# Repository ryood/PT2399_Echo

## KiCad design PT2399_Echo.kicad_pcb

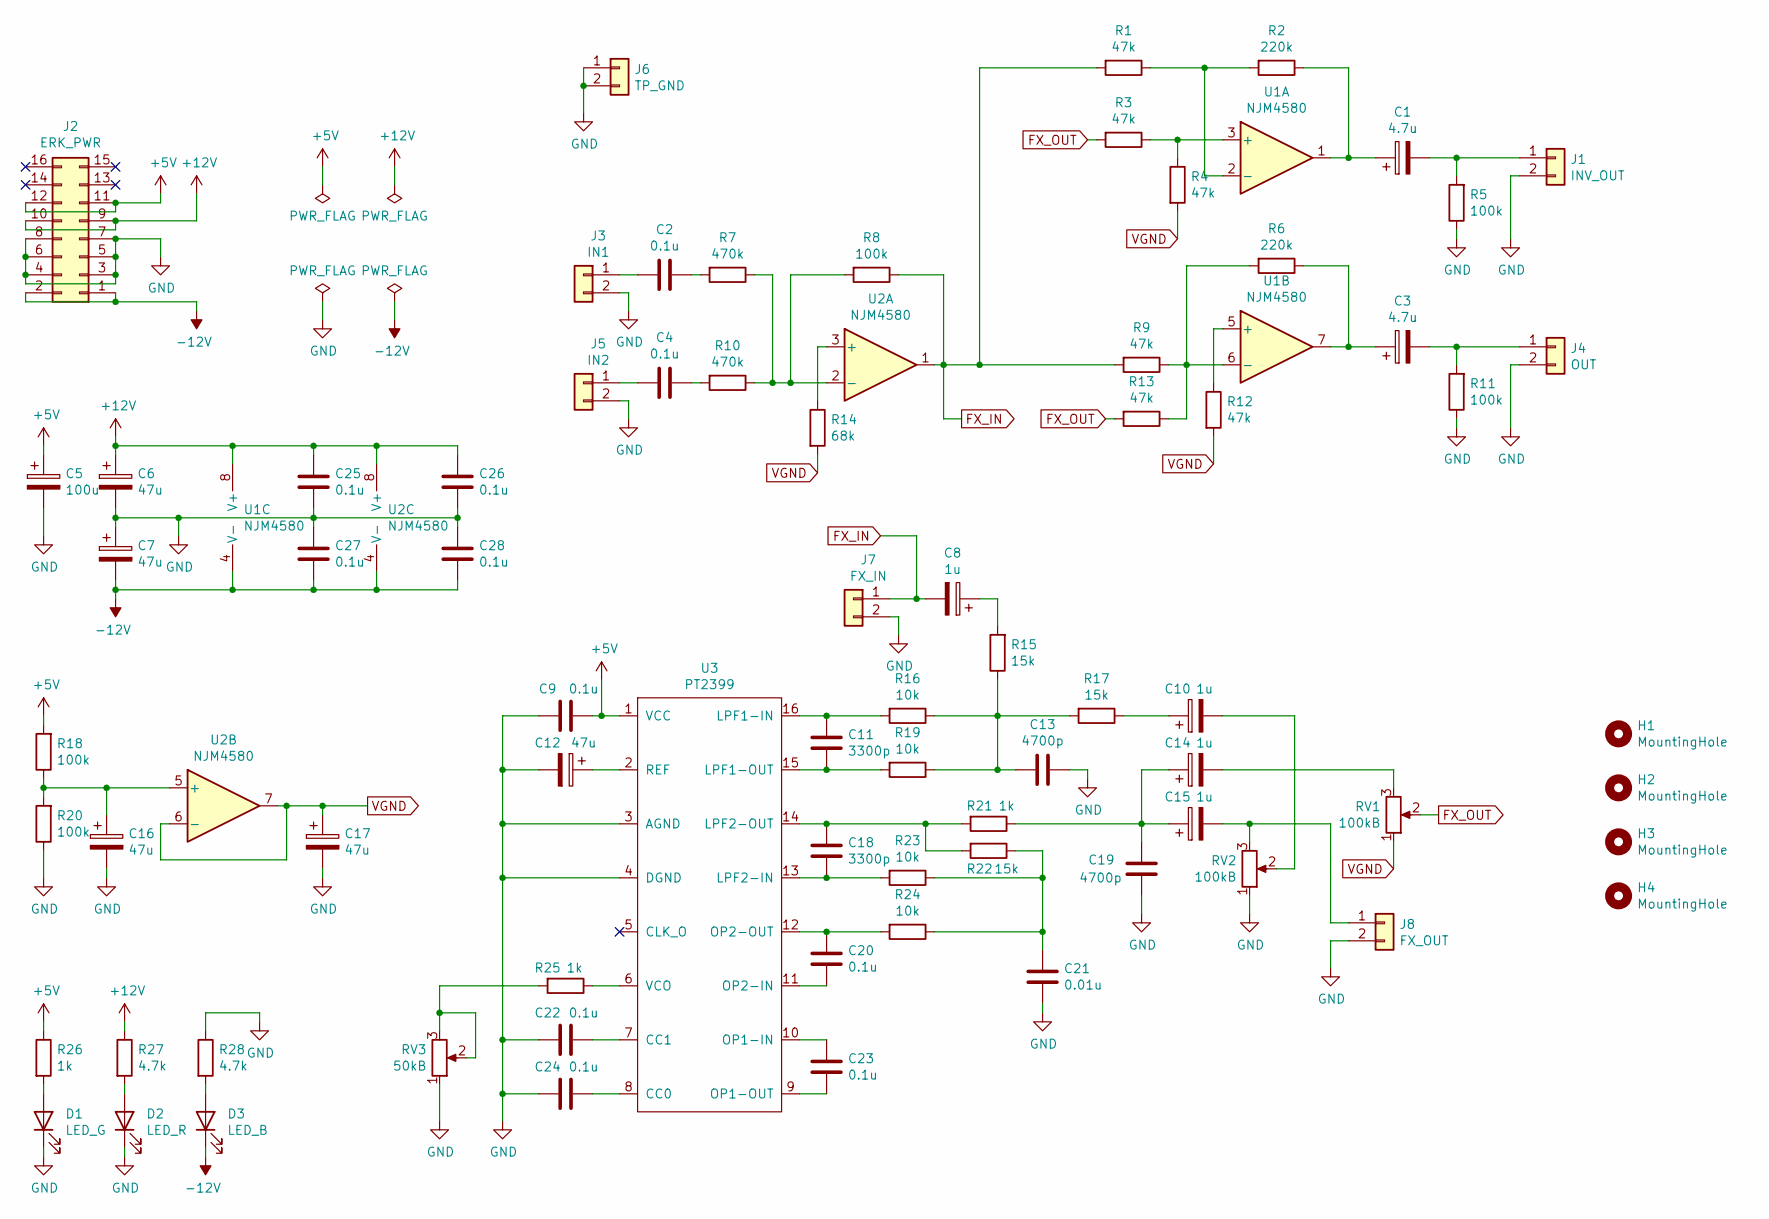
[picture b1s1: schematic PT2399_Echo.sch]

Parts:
C1, C3: 4.7u; CP_Radial_D6.3mm_P2.50mm
C2, C4, C20, C23: 0.1u; C_Rect_L7.2mm_W3.5mm_P5.00mm_FKS2_FKP2_MKS2_MKP2
C5: 100u; CP_Radial_D6.3mm_P2.50mm
C6, C7, C12, C16, C17: 47u; CP_Radial_D6.3mm_P2.50mm
C8, C10, C14, C15: 1u; CP_Radial_D6.3mm_P2.50mm
C9: 0.1u; C_Disc_D4.3mm_W1.9mm_P5.00mm
C11, C18: 3300p; C_Rect_L7.0mm_W3.5mm_P5.00mm
C13, C19: 4700p; C_Rect_L7.0mm_W3.5mm_P5.00mm
C21: 0.01u; C_Rect_L7.2mm_W3.5mm_P5.00mm_FKS2_FKP2_MKS2_MKP2
C22, C24, C25, C26, C27, C28: 0.1u; C_Disc_D3.0mm_W1.6mm_P2.50mm
D1: LED_G; LED_D3.0mm
D2: LED_R; LED_D3.0mm
D3: LED_B; LED_D3.0mm
H1, H2, H3, H4: MountingHole; MountingHole_3.2mm_M3
J1: INV_OUT; JST_XH_B2B-XH-A_1x02_P2.50mm_Vertical
J2: ERK_PWR; IDC-Header_2x08_P2.54mm_Vertical
J3: IN1; JST_XH_B2B-XH-A_1x02_P2.50mm_Vertical
J4: OUT; JST_XH_B2B-XH-A_1x02_P2.50mm_Vertical
J5: IN2; JST_XH_B2B-XH-A_1x02_P2.50mm_Vertical
J6: TP_GND; PinHeader_1x02_P2.54mm_Vertical
J7: FX_IN; JST_XH_B2B-XH-A_1x02_P2.50mm_Vertical
J8: FX_OUT; JST_XH_B2B-XH-A_1x02_P2.50mm_Vertical
R1, R3, R4, R9, R12, R13: 47k; R_Axial_DIN0207_L6.3mm_D2.5mm_P10.16mm_Horizontal
R2, R6: 220k; R_Axial_DIN0207_L6.3mm_D2.5mm_P10.16mm_Horizontal
R5, R8, R11, R18, R20: 100k; R_Axial_DIN0207_L6.3mm_D2.5mm_P10.16mm_Horizontal
R7, R10: 470k; R_Axial_DIN0207_L6.3mm_D2.5mm_P10.16mm_Horizontal
R14: 68k; R_Axial_DIN0207_L6.3mm_D2.5mm_P10.16mm_Horizontal
R15, R17, R22: 15k; R_Axial_DIN0207_L6.3mm_D2.5mm_P10.16mm_Horizontal
R16, R19, R23, R24: 10k; R_Axial_DIN0207_L6.3mm_D2.5mm_P10.16mm_Horizontal
R21, R25, R26: 1k; R_Axial_DIN0207_L6.3mm_D2.5mm_P10.16mm_Horizontal
R27, R28: 4.7k; R_Axial_DIN0207_L6.3mm_D2.5mm_P10.16mm_Horizontal
RV1, RV2: 100kB; Potentiometer_Alps_RK097_Single_Horizontal
RV3: 50kB; Potentiometer_Alps_RK097_Single_Horizontal
U1, U2: NJM4580; DIP-8_W7.62mm_Socket_LongPads
U3: PT2399; DIP-16_W7.62mm_Socket_LongPads

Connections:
+5V: C5.1, C9.1, J2.11, J2.12, R18.2, R26.1, U3.1 (VCC)
+12V: C6.1, C25.1, C26.1, J2.9, J2.10, R27.1, U1.8 (V+), U2.8 (V+)
-12V: C7.2, C27.2, C28.2, D3.1 (K), J2.1, J2.2, U1.4 (V-), U2.4 (V-)
FX_IN: C8.2, J7.1, R1.2, R8.1, R9.2, U2.1
FX_OUT: R3.2, R13.2, RV1.2
GND: C5.2, C6.2, C7.1, C9.2, C12.2, C13.1, C16.2, C17.2, C19.2, C21.2, C22.2, C24.2, C25.2, C26.2, C27.1, C28.1, D1.1 (K), D2.1 (K), J1.2, J2.3, J2.4, J2.5, J2.6, J2.7, J2.8, J3.2, J4.2, J5.2, J6.1, J6.2, J7.2, J8.2, R5.1, R11.1, R20.1, R28.1, RV2.1, RV3.1, U3.3 (AGND), U3.4 (DGND)
unnamed: C1.1, R2.1, U1.1
unnamed: C1.2, J1.1, R5.2
unnamed: C2.1, R7.2
unnamed: C2.2, J3.1
unnamed: C3.1, R6.1, U1.7
unnamed: C3.2, J4.1, R11.2
unnamed: C4.1, R10.2
unnamed: C4.2, J5.1
unnamed: C8.1, R15.2
unnamed: C10.1, R17.1
unnamed: C10.2, RV2.2
unnamed: C11.1, R16.2, U3.16 (LPF1-IN)
unnamed: C11.2, R19.2, U3.15 (LPF1-OUT)
unnamed: C12.1, U3.2 (REF)
unnamed: C13.2, R15.1, R16.1, R17.2, R19.1
unnamed: C14.1, C15.1, C19.1, R21.1
unnamed: C14.2, RV1.3
unnamed: C15.2, J8.1, RV2.3
unnamed: C16.1, R18.1, R20.2, U2.5 (+)
unnamed: C18.1, R21.2, R22.2, U3.14 (LPF2-OUT)
unnamed: C18.2, R23.2, U3.13 (LPF2-IN)
unnamed: C20.1, R24.2, U3.12 (OP2-OUT)
unnamed: C20.2, U3.11 (OP2-IN)
unnamed: C21.1, R22.1, R23.1, R24.1
unnamed: C22.1, U3.7 (CC1)
unnamed: C23.1, U3.10 (OP1-IN)
unnamed: C23.2, U3.9 (OP1-OUT)
unnamed: C24.1, U3.8 (CC0)
unnamed: D1.2 (A), R26.2
unnamed: D2.2 (A), R27.2
unnamed: D3.2 (A), R28.2
unnamed: R1.1, R2.2, U1.2 (-)
unnamed: R3.1, R4.1, U1.3 (+)
unnamed: R7.1, R8.2, R10.1, U2.2 (-)
unnamed: R12.1, U1.5 (+)
unnamed: R6.2, R9.1, R13.1, U1.6 (-)
unnamed: R14.1, U2.3 (+)
unnamed: R25.1, U3.6 (VCO)
unnamed: R25.2, RV3.2, RV3.3
VGND: C17.1, R4.2, R12.2, R14.2, RV1.1, U2.6 (-), U2.7

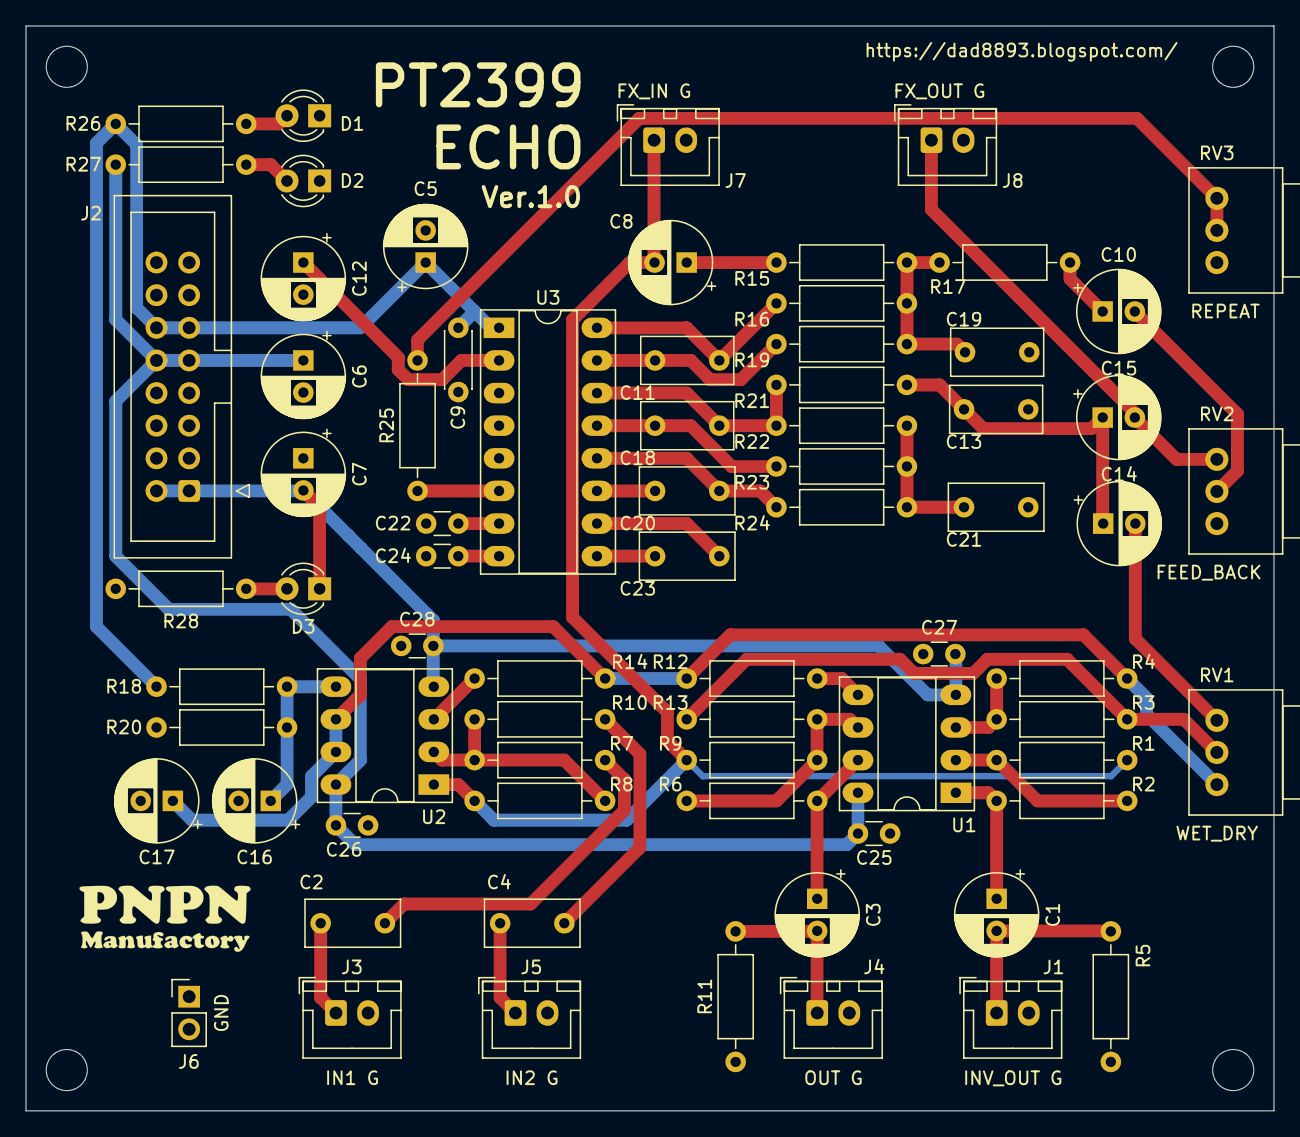
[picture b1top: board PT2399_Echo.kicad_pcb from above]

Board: 2 copper layers, 97.2 x 84.5 mm, 77 parts (0 on the bottom side), 46 nets.

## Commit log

2021-07-19 first comit
2021-08-14 Gerber
2021-09-14 Blog
2021-09-14 Add .gitignore
2021-09-22 Panel Mount
2022-02-12 2nd Unit
